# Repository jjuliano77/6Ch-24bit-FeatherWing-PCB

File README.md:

# 6Ch 24bit FeatherWing Design Files

This is a simple but versatile [Feather](https://learn.adafruit.com/adafruit-feather/feather-specification) compatible board. It uses an [AD7794](https://www.analog.com/media/en/technical-documentation/data-sheets/AD7794_7795.pdf), a very robust 6 channel 24 bit ADC. It's a relatively slow converter (470 Hz Max), but this board is really suited for lower power, monitoring type applications and can consume as little as 2 μA in standby. It has an on-board 2.5 V regulator for excitation voltage and is designed primarily to read load cells and pressure gauges. However, it can also be used to read any ratiometric sensor (such as potentiometers), thermocouples, or any 0 - 3.3 V signal.

**Specifications**

- RMS noise down to 40 nV at lowest data rate (4.17 Hz)
- Power-down current: 1 μA maximum (AD7794 chip) 
- Low noise, programmable gain, instrumentation amplifier
- Band gap reference with 4 ppm/°C drift typical
- Simultaneous 50 Hz/60 Hz rejection
- Update rate: 4.17 Hz to 470 Hz
- Six differential analog inputs
- 4 pin connections with excitation and ground for each channel
- On board 2.5v LDO with enable pin broken out to turn off excitation for low power applications

The board can be used with screw terminals, Plug in spring terminal connectors, or pin headers for the sensor connections

This board can be purchased assembled here: [6-ch-24-bit-full-bridge-sensor-featherwing](https://www.tindie.com/products/jtinker/6-ch-24-bit-full-bridge-sensor-featherwing/)

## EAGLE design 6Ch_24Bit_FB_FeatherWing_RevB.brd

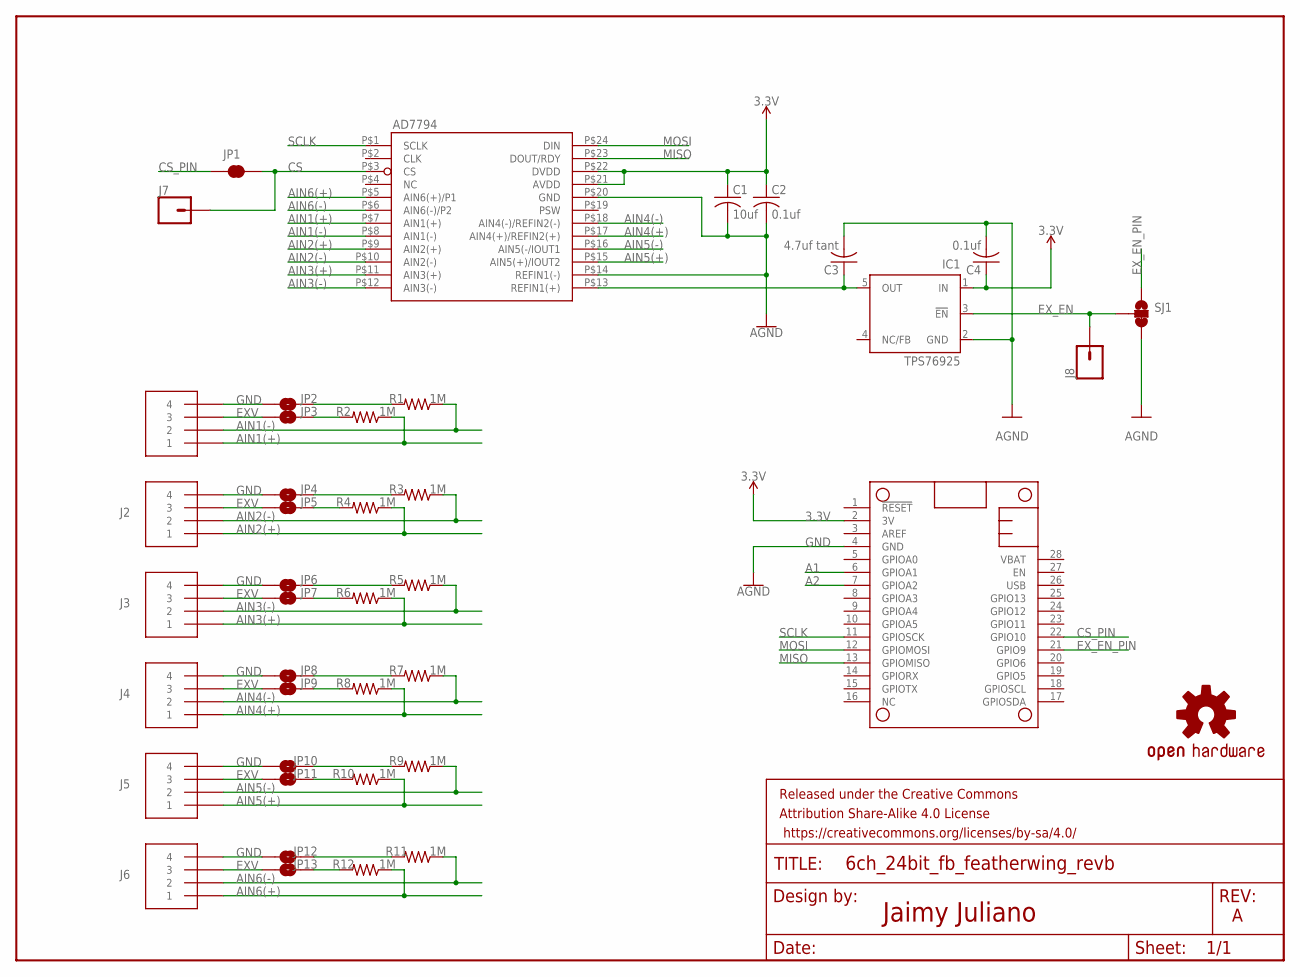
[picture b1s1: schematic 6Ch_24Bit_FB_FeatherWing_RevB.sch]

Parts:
C1: 10uf; C0603
C2, C4: 0.1uf; C0603
C3: 4.7uf tant; C1206K
FRAME2: FRAME-LETTER; CREATIVE_COMMONS
IC1: TPS76925; SOT23-DBV
J1, J2, J3, J4, J5, J6: CON_PTSM_SOCKET-4-PTH-VERT
J7, J8: CONN_01PTH_NO_SILK_YES_STOP; 1X01_NO_SILK
JP1: JUMPER-SMT_2_NC_TRACE_NO-SILK; SMT-JUMPER_2_NC_TRACE_NO-SILK
JP2, JP3, JP4, JP5, JP6, JP7, JP8, JP9, JP10, JP11, JP12, JP13: JUMPER-SMT_2_NO_SILK; SMT-JUMPER_2_NO_SILK
LOGO1: OSHW-LOGOS; OSHW-LOGO-S
MS1: FEATHERWING_NODIM; FEATHERWING_DIM
R1, R2, R3, R4, R5, R6, R7, R8, R9, R10, R11, R12: 1M; 0603
SJ1: JUMPER-SMT_3_1-NC_TRACE_NO-SILK; SMT-JUMPER_3_1-NC_TRACE_NO-SILK
U1: AD7794; TSSOP-24

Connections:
3.3V: C1.1, C2.1, C4.1, IC1.1 (IN), MS1.2 (3V), U1.P$21 (AVDD), U1.P$22 (DVDD)
A1: MS1.6 (GPIOA1)
A2: MS1.7 (GPIOA2)
AIN1(+): J1.P$1 (1), R2.1, U1.P$7 (AIN1(+))
AIN1(-): J1.P$2 (2), R1.1, U1.P$8 (AIN1(-))
AIN2(+): J2.P$1 (1), R4.1, U1.P$9 (AIN2(+))
AIN2(-): J2.P$2 (2), R3.1, U1.P$10 (AIN2(-))
AIN3(+): J3.P$1 (1), R6.1, U1.P$11 (AIN3(+))
AIN3(-): J3.P$2 (2), R5.1, U1.P$12 (AIN3(-))
AIN4(+): J4.P$1 (1), R8.1, U1.P$17 (AIN4(+)/REFIN2(+))
AIN4(-): J4.P$2 (2), R7.1, U1.P$18 (AIN4(-)/REFIN2(-))
AIN5(+): J5.P$1 (1), R10.1, U1.P$15 (AIN5(+)/IOUT2)
AIN5(-): J5.P$2 (2), R9.1, U1.P$16 (AIN5(-/IOUT1)
AIN6(+): J6.P$1 (1), R12.1, U1.P$5 (AIN6(+)/P1)
AIN6(-): J6.P$2 (2), R11.1, U1.P$6 (AIN6(-)/P2)
CS: J7.1, JP1.2, U1.P$3 (CS)
CS_PIN: JP1.1, MS1.22 (GPIO10)
EXV: C3.1, IC1.5 (OUT), J1.P$3 (3), J2.P$3 (3), J3.P$3 (3), J4.P$3 (3), J5.P$3 (3), J6.P$3 (3), JP3.2, JP5.2, JP7.2, JP9.2, JP11.2, JP13.2, U1.P$13 (REFIN1(+))
EX_EN: IC1.3 (!EN), J8.1, SJ1.2
EX_EN_PIN: MS1.21 (GPIO9), SJ1.1
GND: C1.2, C2.2, C3.2, C4.2, IC1.2 (GND), J1.P$4 (4), J2.P$4 (4), J3.P$4 (4), J4.P$4 (4), J5.P$4 (4), J6.P$4 (4), JP2.2, JP4.2, JP6.2, JP8.2, JP10.2, JP12.2, MS1.4 (GND), SJ1.3, U1.P$14 (REFIN1(-)), U1.P$20 (GND)
MISO: MS1.13 (GPIOMISO), U1.P$23 (DOUT/RDY)
MOSI: MS1.12 (GPIOMOSI), U1.P$24 (DIN)
unnamed: JP3.1, R2.2
unnamed: JP2.1, R1.2
unnamed: JP5.1, R4.2
unnamed: JP4.1, R3.2
unnamed: JP7.1, R6.2
unnamed: JP6.1, R5.2
unnamed: JP9.1, R8.2
unnamed: JP8.1, R7.2
unnamed: JP11.1, R10.2
unnamed: JP10.1, R9.2
unnamed: JP13.1, R12.2
unnamed: JP12.1, R11.2
SCLK: MS1.11 (GPIOSCK), U1.P$1 (SCLK)

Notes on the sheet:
Jaimy Juliano

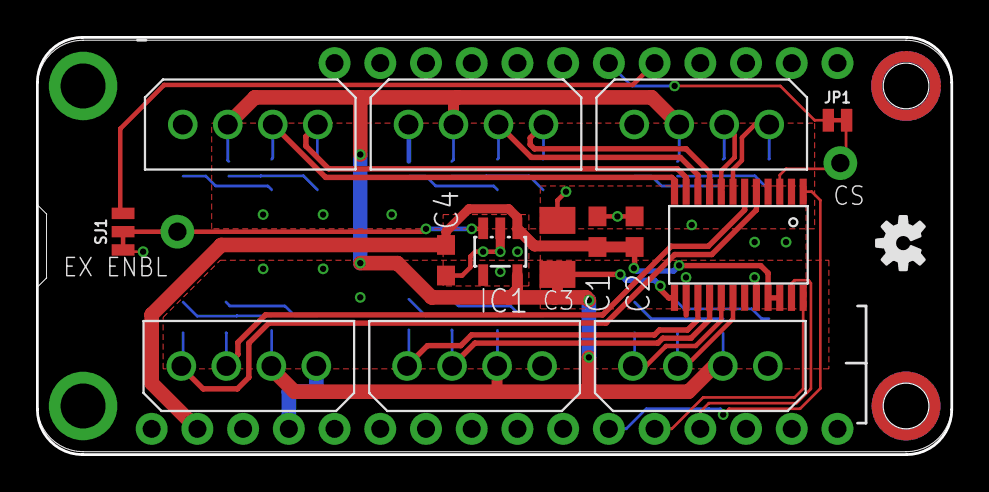
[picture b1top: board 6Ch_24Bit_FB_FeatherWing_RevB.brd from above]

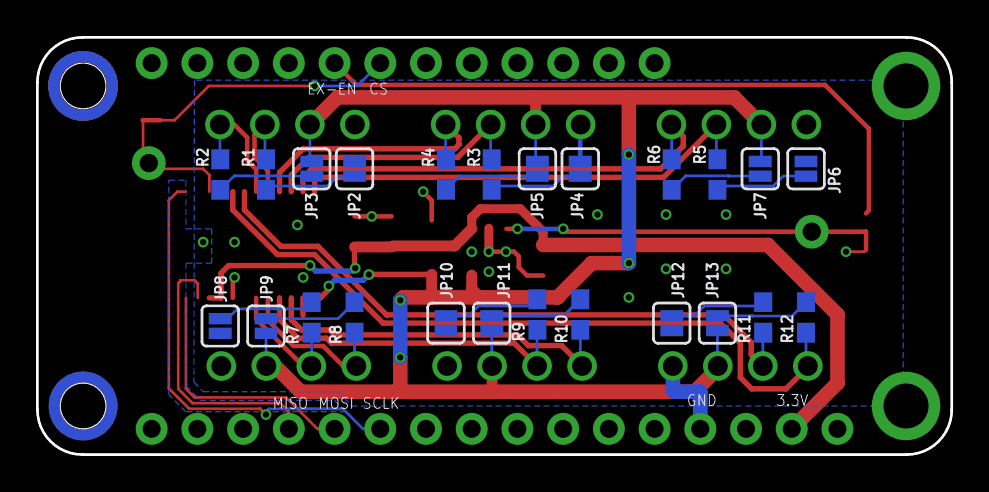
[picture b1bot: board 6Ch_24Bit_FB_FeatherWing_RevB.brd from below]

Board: 2 copper layers, 50.8 x 23.2 mm, 43 parts (24 on the bottom side), 34 nets.

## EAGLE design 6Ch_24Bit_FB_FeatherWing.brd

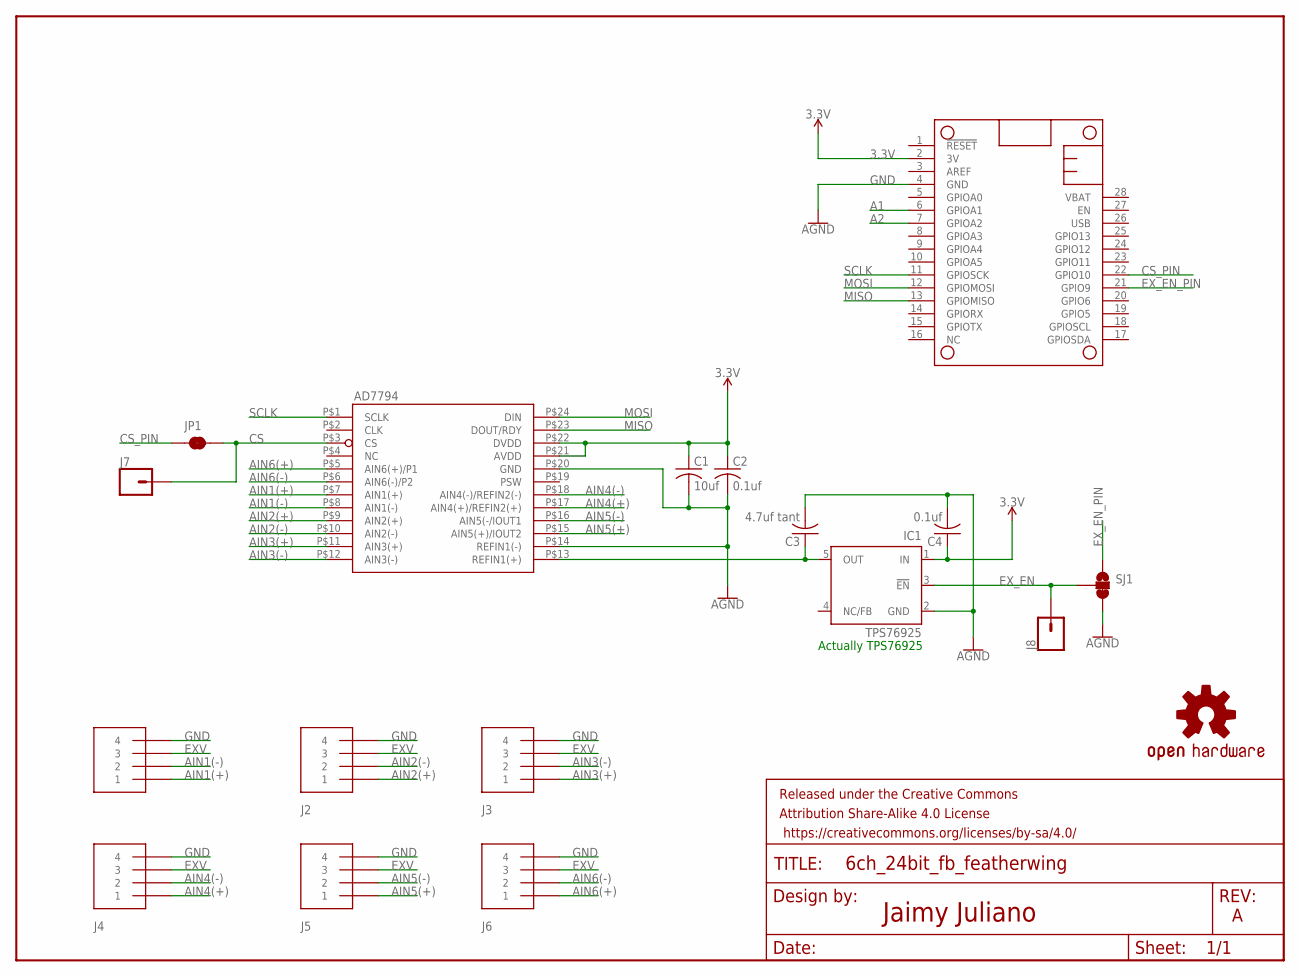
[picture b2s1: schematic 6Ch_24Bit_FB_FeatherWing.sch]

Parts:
C1: 10uf; C0603
C2, C4: 0.1uf; C0603
C3: 4.7uf tant; C1206K
FRAME2: FRAME-LETTER; CREATIVE_COMMONS
IC1: TPS76925; SOT23-DBV
J1, J2, J3, J4, J5, J6: CON_PTSM_SOCKET-4-PTH-VERT
J7, J8: CONN_01PTH_NO_SILK_YES_STOP; 1X01_NO_SILK
JP1: JUMPER-SMT_2_NC_TRACE_NO-SILK; SMT-JUMPER_2_NC_TRACE_NO-SILK
LOGO1: OSHW-LOGOS; OSHW-LOGO-S
MS1: FEATHERWING_NODIM; FEATHERWING_DIM
SJ1: JUMPER-SMT_3_1-NC_TRACE_NO-SILK; SMT-JUMPER_3_1-NC_TRACE_NO-SILK
U1: AD7794; TSSOP-24

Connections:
3.3V: C1.1, C2.1, C4.1, IC1.1 (IN), MS1.2 (3V), U1.P$21 (AVDD), U1.P$22 (DVDD)
A1: MS1.6 (GPIOA1)
A2: MS1.7 (GPIOA2)
AIN1(+): J1.P$1 (1), U1.P$7 (AIN1(+))
AIN1(-): J1.P$2 (2), U1.P$8 (AIN1(-))
AIN2(+): J2.P$1 (1), U1.P$9 (AIN2(+))
AIN2(-): J2.P$2 (2), U1.P$10 (AIN2(-))
AIN3(+): J3.P$1 (1), U1.P$11 (AIN3(+))
AIN3(-): J3.P$2 (2), U1.P$12 (AIN3(-))
AIN4(+): J4.P$1 (1), U1.P$17 (AIN4(+)/REFIN2(+))
AIN4(-): J4.P$2 (2), U1.P$18 (AIN4(-)/REFIN2(-))
AIN5(+): J5.P$1 (1), U1.P$15 (AIN5(+)/IOUT2)
AIN5(-): J5.P$2 (2), U1.P$16 (AIN5(-/IOUT1)
AIN6(+): J6.P$1 (1), U1.P$5 (AIN6(+)/P1)
AIN6(-): J6.P$2 (2), U1.P$6 (AIN6(-)/P2)
CS: J7.1, JP1.2, U1.P$3 (CS)
CS_PIN: JP1.1, MS1.22 (GPIO10)
EXV: C3.1, IC1.5 (OUT), J1.P$3 (3), J2.P$3 (3), J3.P$3 (3), J4.P$3 (3), J5.P$3 (3), J6.P$3 (3), U1.P$13 (REFIN1(+))
EX_EN: IC1.3 (!EN), J8.1, SJ1.2
EX_EN_PIN: MS1.21 (GPIO9), SJ1.1
GND: C1.2, C2.2, C3.2, C4.2, IC1.2 (GND), J1.P$4 (4), J2.P$4 (4), J3.P$4 (4), J4.P$4 (4), J5.P$4 (4), J6.P$4 (4), MS1.4 (GND), SJ1.3, U1.P$14 (REFIN1(-)), U1.P$20 (GND)
MISO: MS1.13 (GPIOMISO), U1.P$23 (DOUT/RDY)
MOSI: MS1.12 (GPIOMOSI), U1.P$24 (DIN)
SCLK: MS1.11 (GPIOSCK), U1.P$1 (SCLK)

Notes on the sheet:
Actually TPS76925
Jaimy Juliano

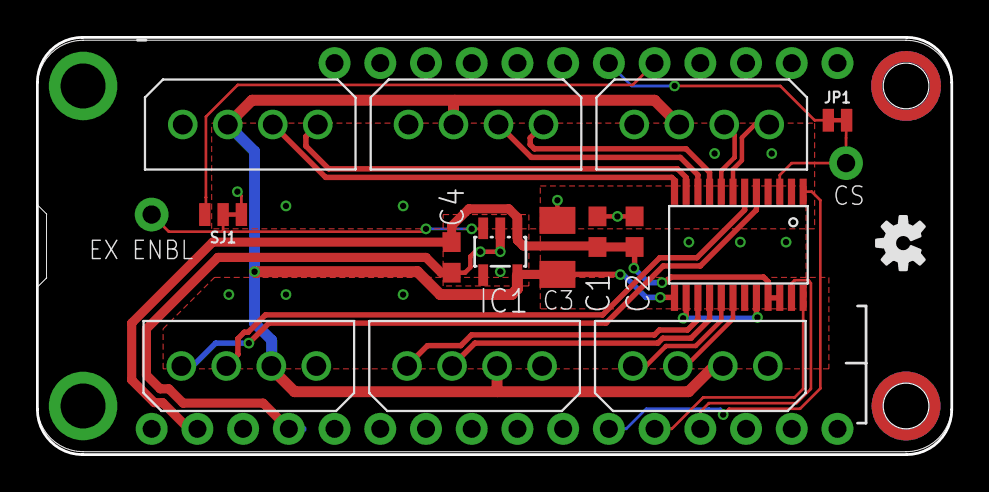
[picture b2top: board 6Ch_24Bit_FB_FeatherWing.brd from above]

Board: 2 copper layers, 50.8 x 23.2 mm, 19 parts (0 on the bottom side), 22 nets.

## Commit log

2021-01-09 Updated to current hardware version

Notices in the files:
parts and their libraries:
SparkFun-Connectors: Licensing: Creative Commons ShareAlike 4.0 International - https://creativecommons.org/licenses/by-sa/4.0
SparkFun-Aesthetics: Released under the Creative Commons Attribution Share-Alike 4.0 License
SparkFun-Aesthetics: https://creativecommons.org/licenses/by-sa/4.0
